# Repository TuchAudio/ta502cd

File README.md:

# ta502cd
Two-channel stereo mixer, switched

## Purpose
A simple, _DJ-like_ two channel **mixer**. Inputs are intended to be taken from suitable **phono preamps** (like TuchAudio models [101b](../../../ta101b) or [103](../../../ta103)). Two _separately mixed_ outputs are provided, for both **line output** and a **headphone output** for preview.

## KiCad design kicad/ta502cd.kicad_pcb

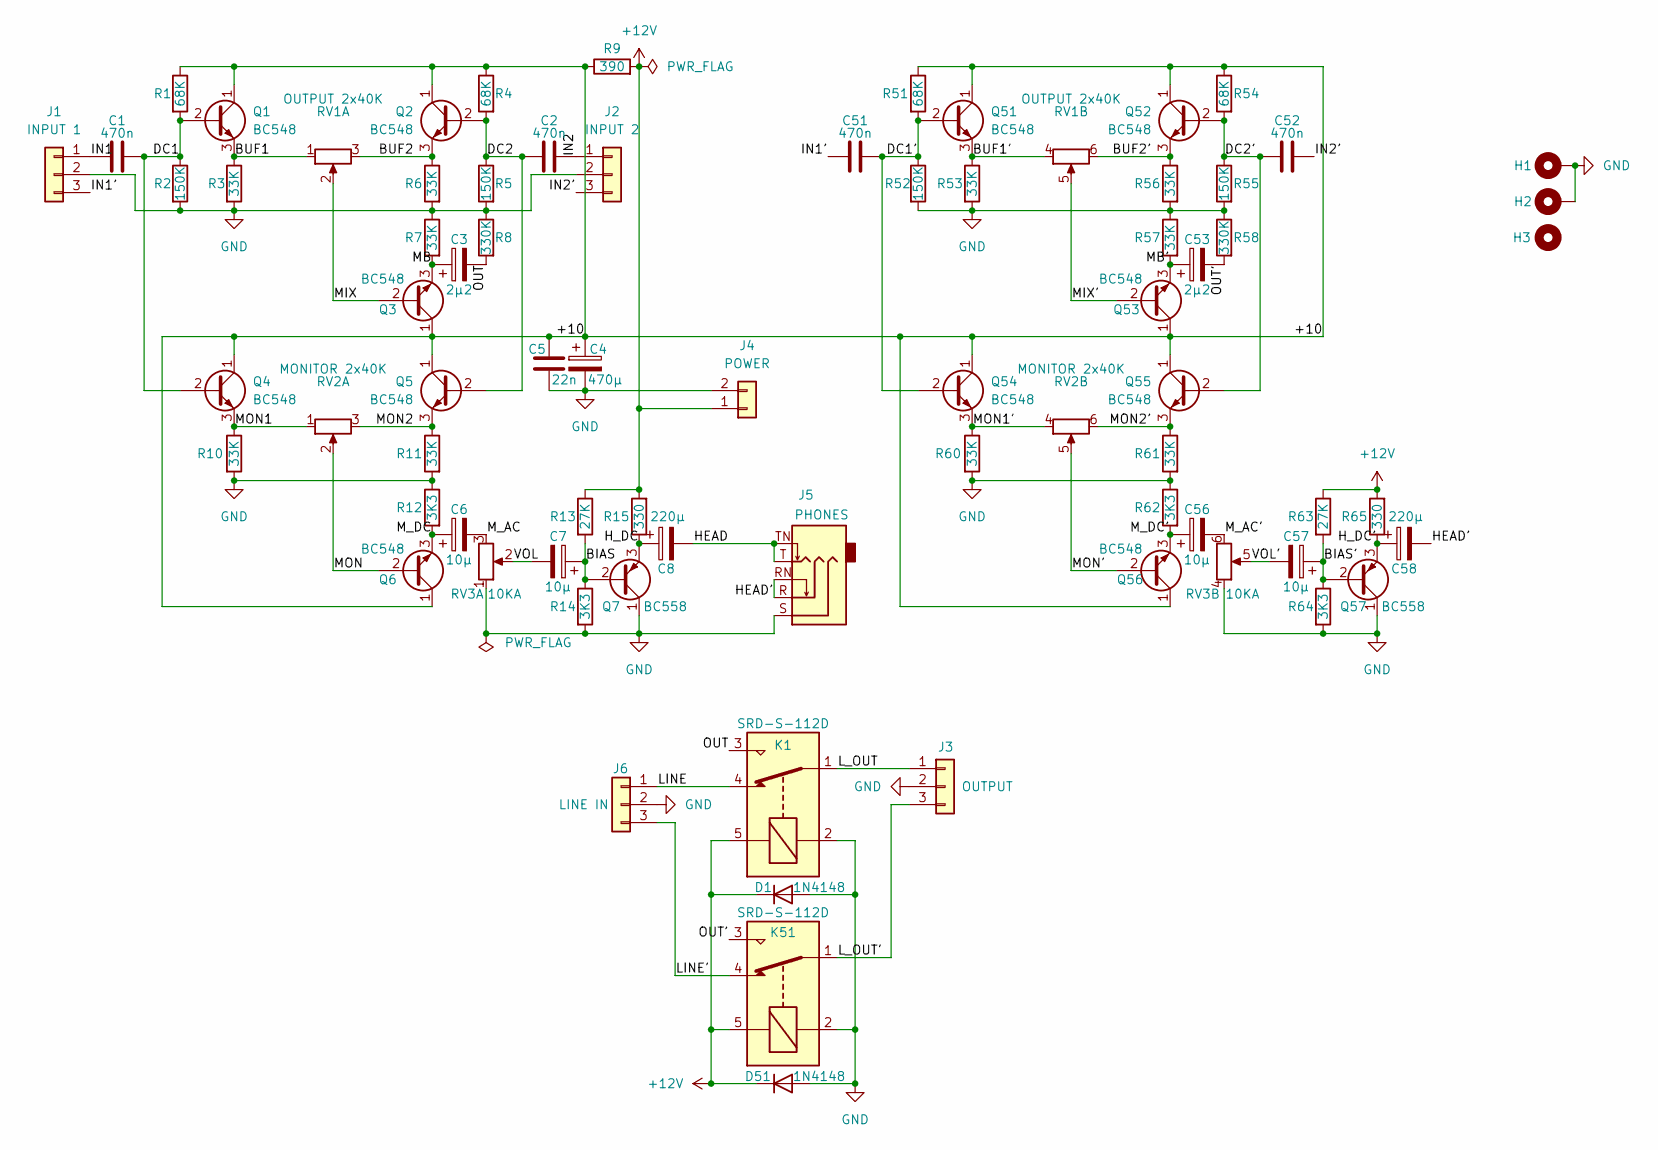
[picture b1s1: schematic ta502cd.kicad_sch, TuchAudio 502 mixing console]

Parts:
C1, C2, C51, C52: 470n; C_Rect_L7.2mm_W3.0mm_P5.00mm_FKS2_FKP2_MKS2_MKP2
C3, C53: 2µ2; CP_Radial_D4.0mm_P1.50mm
C4: 470µ; CP_Radial_D6.3mm_P2.50mm
C5: 22n; C_Disc_D6.0mm_W2.5mm_P5.00mm
C6, C7, C56, C57: 10µ; CP_Radial_D4.0mm_P1.50mm
C8, C58: 220µ; CP_Radial_D6.3mm_P2.50mm
D1, D51: 1N4148; D_DO-35_SOD27_P7.62mm_Horizontal
H1, H2: MountingHole_Pad; MountingHole_3.2mm_M3_DIN965_Pad
H3: MountingHole; MountingHole_3.2mm_M3_DIN965
J1: INPUT 1; PinHeader_1x03_P2.54mm_Vertical
J2: INPUT 2; PinHeader_1x03_P2.54mm_Vertical
J3: OUTPUT; PinHeader_1x03_P2.54mm_Vertical
J4: POWER; PinHeader_1x02_P2.54mm_Vertical
J5: PHONES; Jack_3.5mm_CUI_SJ1-3525N_Horizontal
J6: LINE IN; PinHeader_1x03_P2.54mm_Vertical
K1, K51: SRD-S-112D; Relay_SPDT_SANYOU_SRD_Series_Form_C
Q1, Q2, Q3, Q4, Q5, Q6, Q51, Q52, Q53, Q54, Q55, Q56: BC548; TO-92_Inline
Q7, Q57: BC558; TO-92_Inline
R1, R4, R51, R54: 68K; R_Axial_DIN0207_L6.3mm_D2.5mm_P10.16mm_Horizontal
R2, R5, R52, R55: 150K; R_Axial_DIN0207_L6.3mm_D2.5mm_P10.16mm_Horizontal
R3, R6, R7, R10, R11, R53, R56, R57, R60, R61: 33K; R_Axial_DIN0207_L6.3mm_D2.5mm_P10.16mm_Horizontal
R8, R58: 330K; R_Axial_DIN0207_L6.3mm_D2.5mm_P10.16mm_Horizontal
R9: 390; R_Axial_DIN0207_L6.3mm_D2.5mm_P10.16mm_Horizontal
R12, R14, R62, R64: 3K3; R_Axial_DIN0207_L6.3mm_D2.5mm_P10.16mm_Horizontal
R13, R63: 27K; R_Axial_DIN0207_L6.3mm_D2.5mm_P10.16mm_Horizontal
R15, R65: 330; R_Axial_DIN0309_L9.0mm_D3.2mm_P5.08mm_Vertical
RV1: OUTPUT 2x40K; PinHeader_1x06_P2.54mm_Vertical
RV2: MONITOR 2x40K; PinHeader_1x06_P2.54mm_Vertical
RV3: 10KA; Potentiometer_Alps_225G_Dual_Horizontal

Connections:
+12V: D1.1 (K), D51.1 (K), J4.1, K1.5, K51.5, R9.2, R13.1, R15.2, R63.1, R65.2
/+10: C4.1, C5.1, Q1.1 (C), Q2.1 (C), Q3.1 (C), Q4.1 (C), Q5.1 (C), Q6.1 (C), Q51.1 (C), Q52.1 (C), Q53.1 (C), Q54.1 (C), Q55.1 (C), Q56.1 (C), R1.1, R4.1, R9.1, R51.1, R54.1
/BIAS: C7.1, Q7.2 (B), R13.2, R14.1
/BIAS': C57.1, Q57.2 (B), R63.2, R64.1
/BUF1: Q1.3 (E), R3.1, RV1.1
/BUF1': Q51.3 (E), R53.1, RV1.4
/BUF2: Q2.3 (E), R6.1, RV1.3
/BUF2': Q52.3 (E), R56.1, RV1.6
/DC1: C1.2, Q1.2 (B), Q4.2 (B), R1.2, R2.1
/DC1': C51.2, Q51.2 (B), Q54.2 (B), R51.2, R52.1
/DC2: C2.2, Q2.2 (B), Q5.2 (B), R4.2, R5.1
/DC2': C52.2, Q52.2 (B), Q55.2 (B), R54.2, R55.1
/HEAD: C8.2, J5.T, J5.TN
/HEAD': C58.2, J5.R, J5.RN
/H_DC: C8.1, Q7.3 (E), R15.1
/H_DC': C58.1, Q57.3 (E), R65.1
/IN1: C1.1, J1.1
/IN1': C51.1, J1.3
/IN2: C2.1, J2.1
/IN2': C52.1, J2.3
/LINE: J6.1, K1.4
/LINE': J6.3, K51.4
/L_OUT: J3.1, K1.1
/L_OUT': J3.3, K51.1
/MB: C3.1, Q3.3 (E), R7.2
/MB': C53.1, Q53.3 (E), R57.2
/MIX: Q3.2 (B), RV1.2
/MIX': Q53.2 (B), RV1.5
/MON: Q6.2 (B), RV2.2
/MON1: Q4.3 (E), R10.1, RV2.1
/MON1': Q54.3 (E), R60.1, RV2.4
/MON2: Q5.3 (E), R11.1, RV2.3
/MON2': Q55.3 (E), R61.1, RV2.6
/MON': Q56.2 (B), RV2.5
/M_AC: C6.2, RV3.3
/M_AC': C56.2, RV3.6
/M_DC: C6.1, Q6.3 (E), R12.2
/M_DC': C56.1, Q56.3 (E), R62.2
/OUT: C3.2, K1.3, R8.2
/OUT': C53.2, K51.3, R58.2
/VOL: C7.2, RV3.2
/VOL': C57.2, RV3.5
GND: C4.2, C5.2, D1.2 (A), D51.2 (A), H1.1, H2.1, J1.2, J2.2, J3.2, J4.2, J5.S, J6.2, K1.2, K51.2, Q7.1 (C), Q57.1 (C), R2.2, R3.2, R5.2, R6.2, R7.1, R8.1, R10.2, R11.2, R12.1, R14.2, R52.2, R53.2, R55.2, R56.2, R57.1, R58.1, R60.2, R61.2, R62.1, R64.2, RV3.1, RV3.4

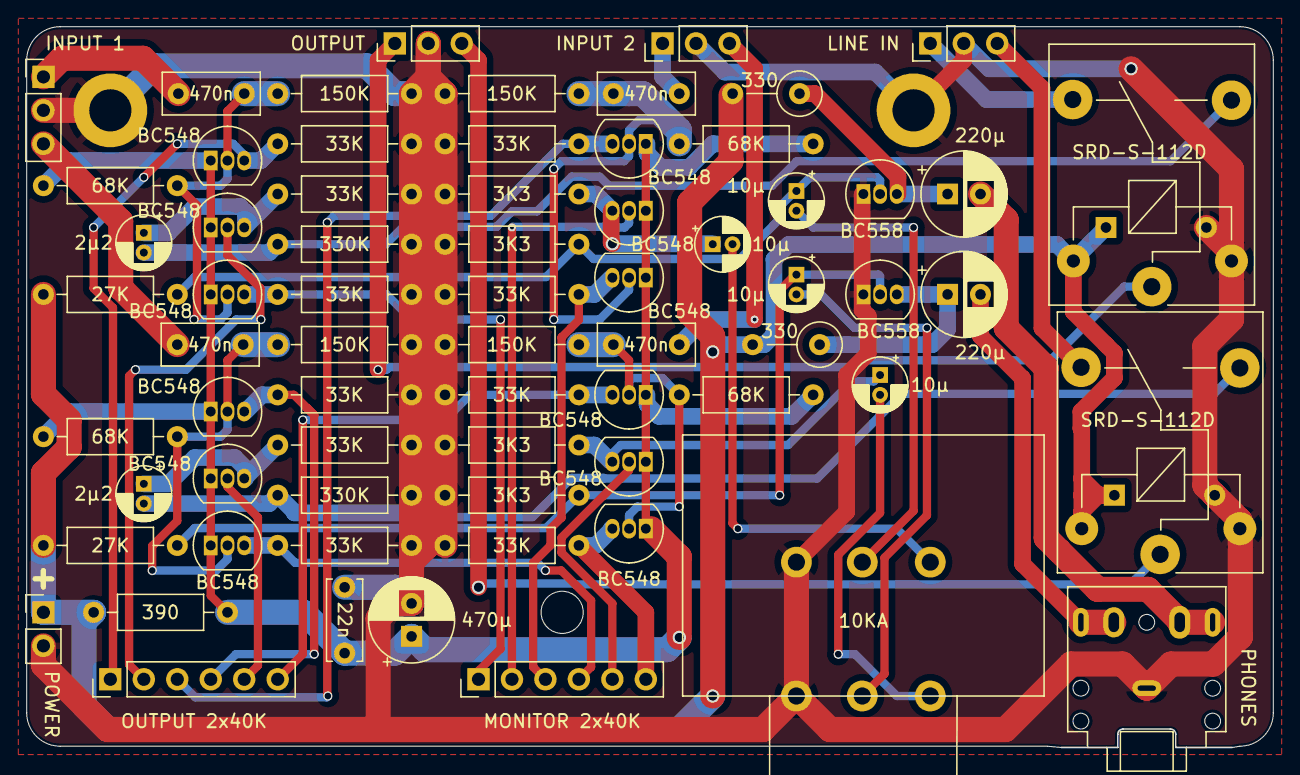
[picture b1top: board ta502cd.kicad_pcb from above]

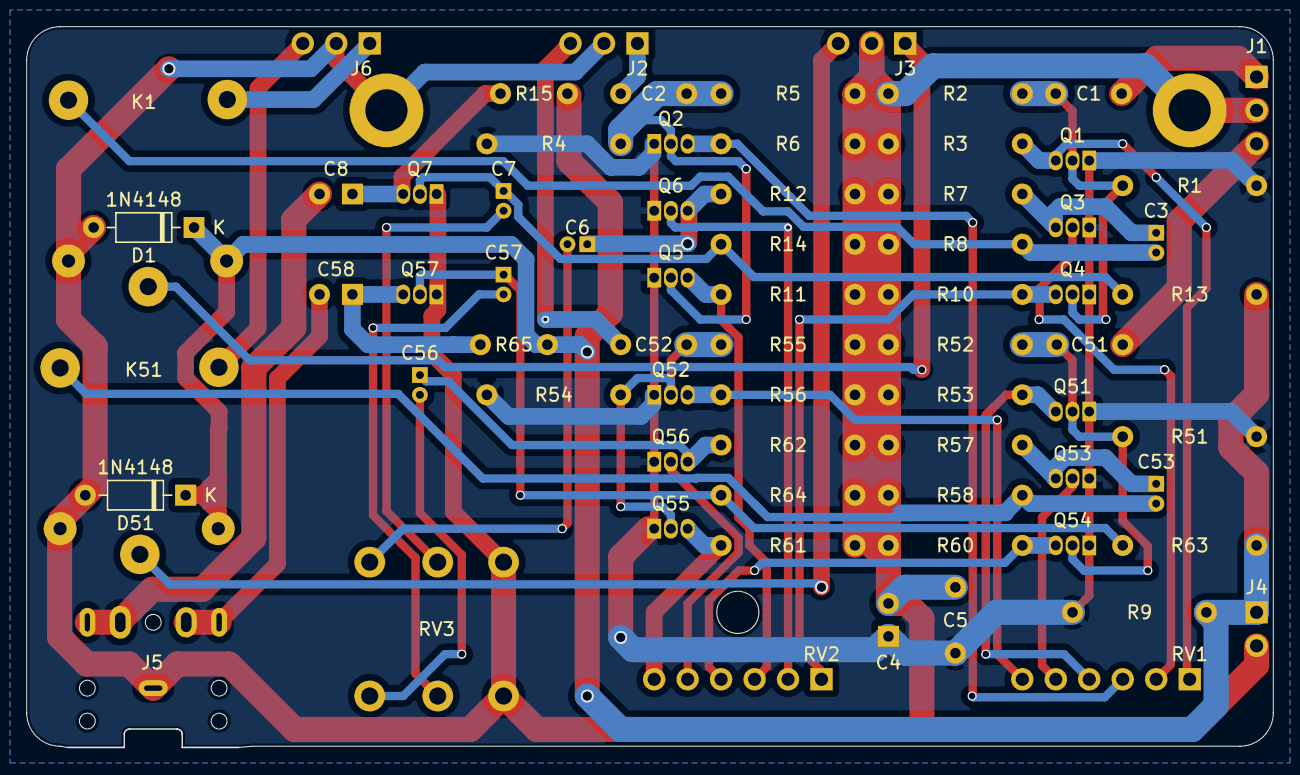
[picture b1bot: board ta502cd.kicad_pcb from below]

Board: 2 copper layers, 94.5 x 54.7 mm, 73 parts (2 on the bottom side), 43 nets.

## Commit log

2025-11-08 add KiCAD files
2025-11-12 basic purpose
2025-11-24 add links
